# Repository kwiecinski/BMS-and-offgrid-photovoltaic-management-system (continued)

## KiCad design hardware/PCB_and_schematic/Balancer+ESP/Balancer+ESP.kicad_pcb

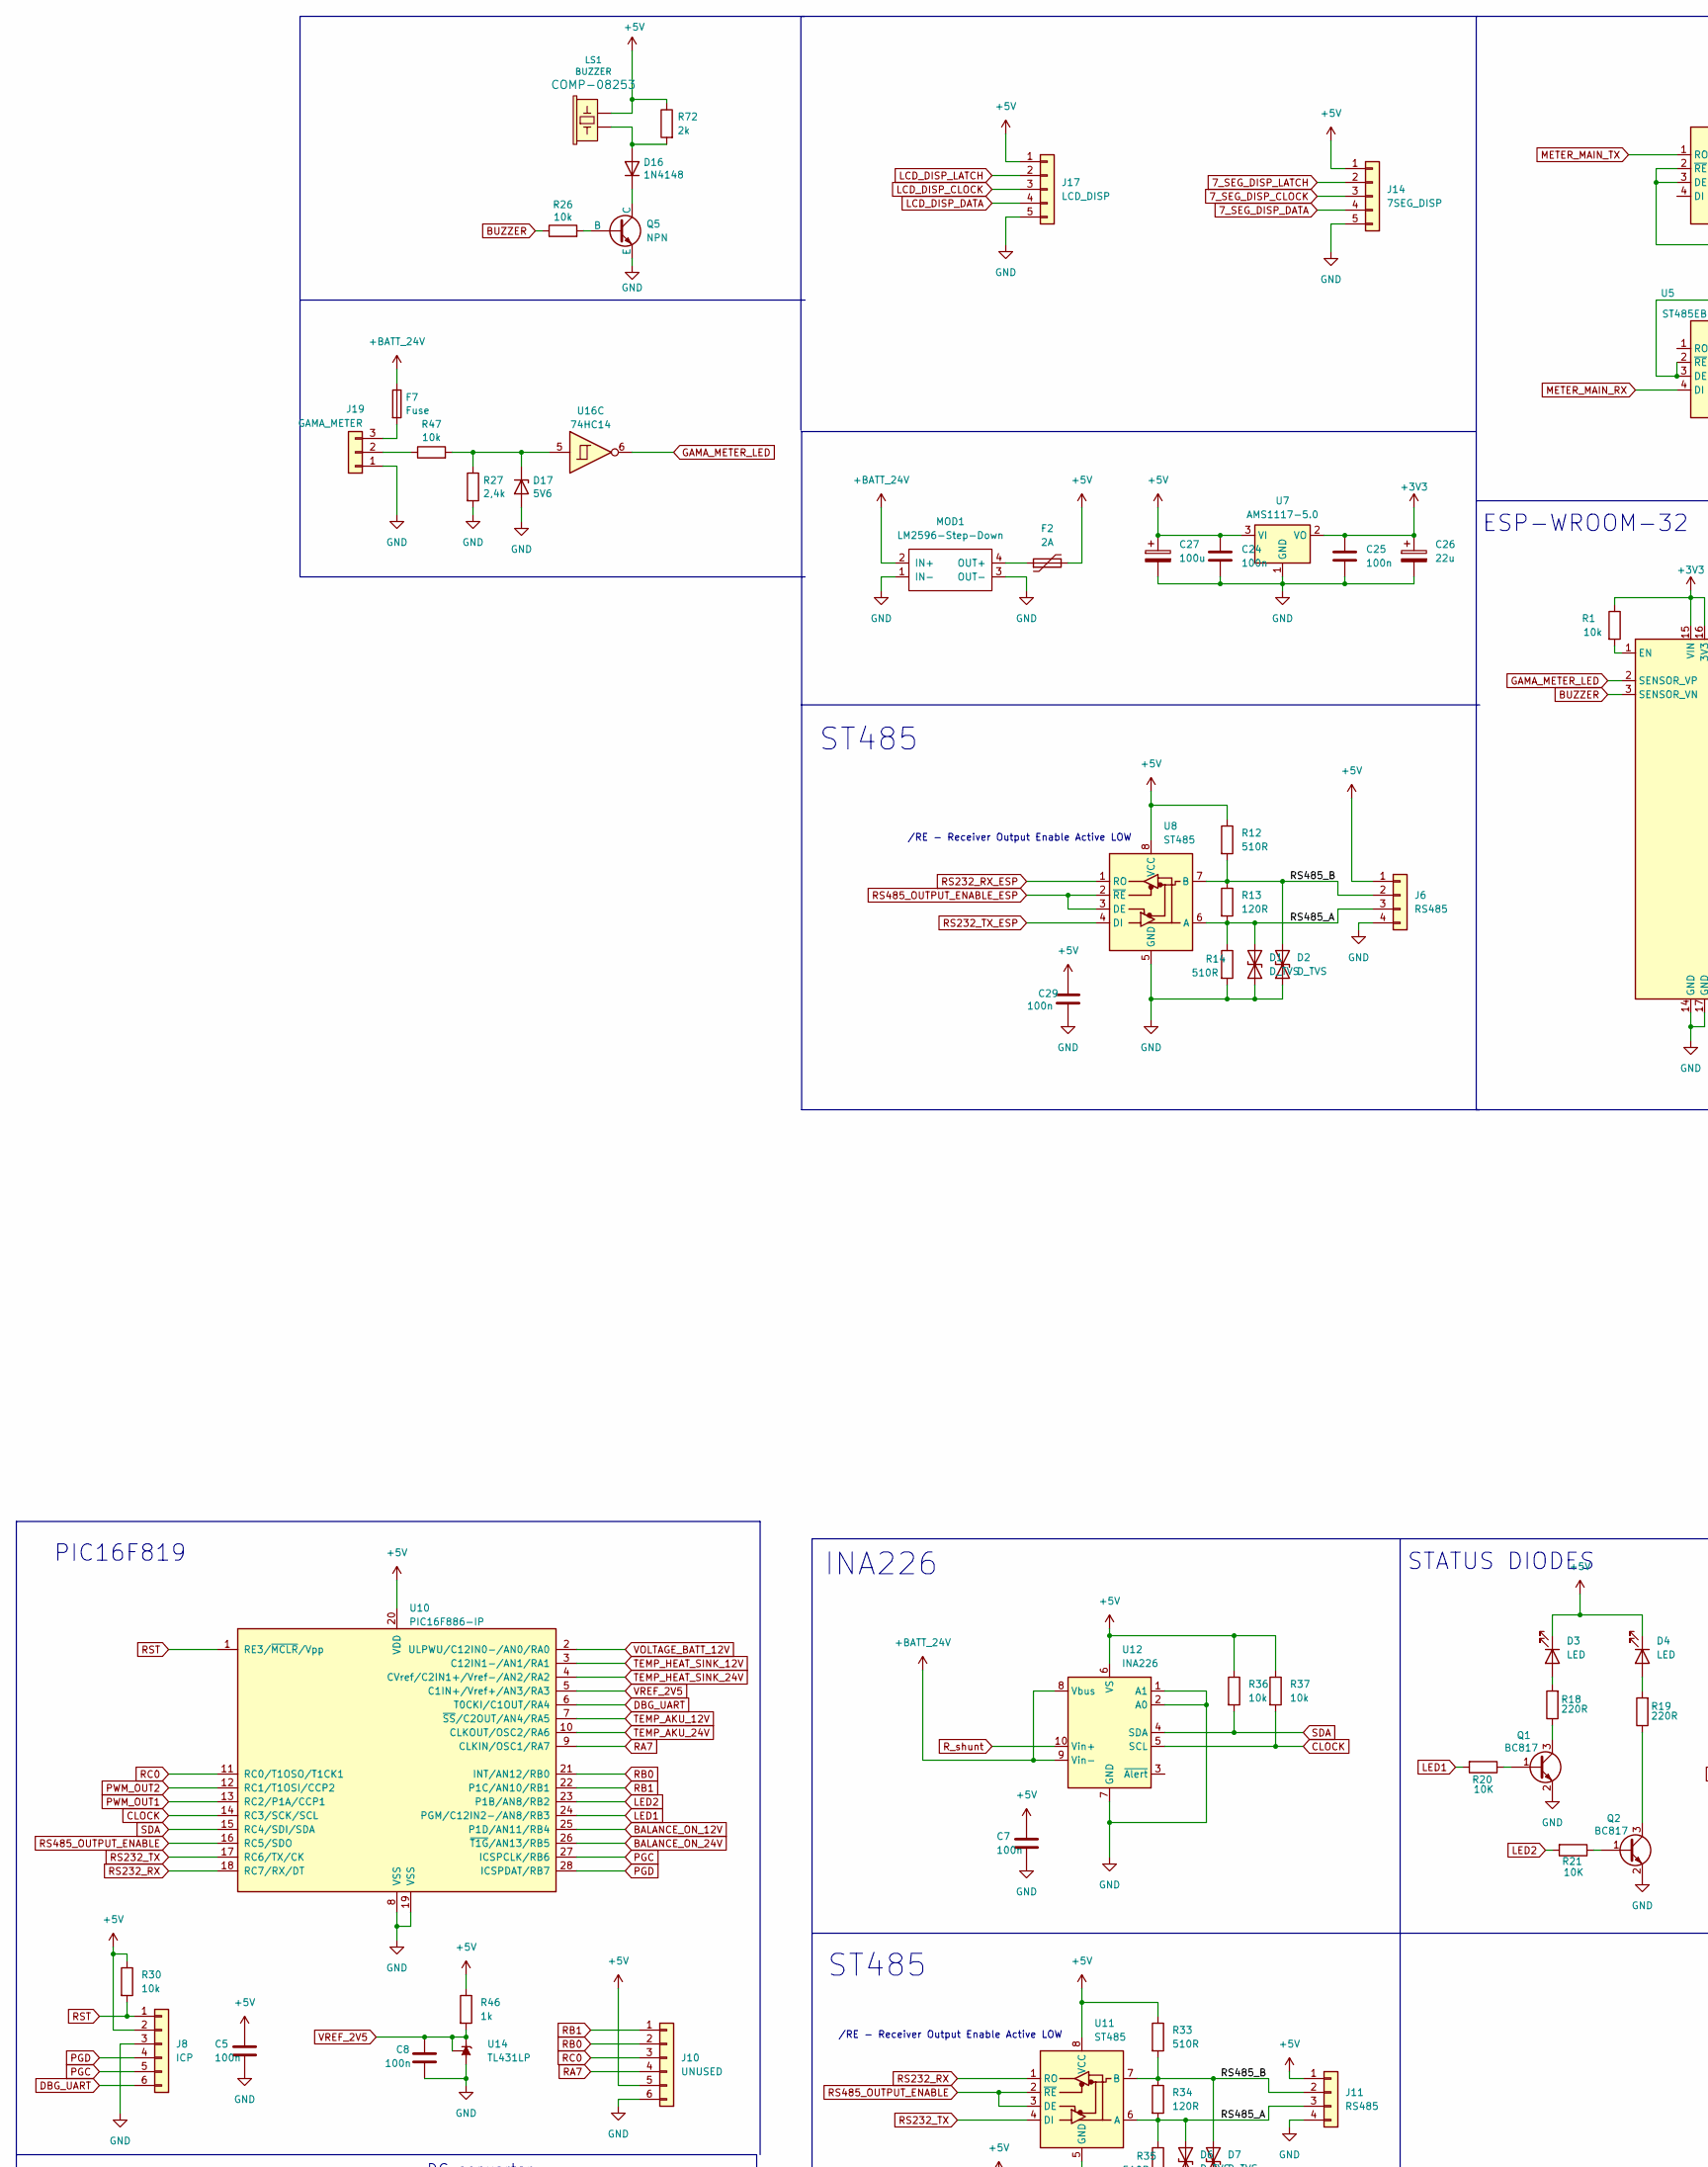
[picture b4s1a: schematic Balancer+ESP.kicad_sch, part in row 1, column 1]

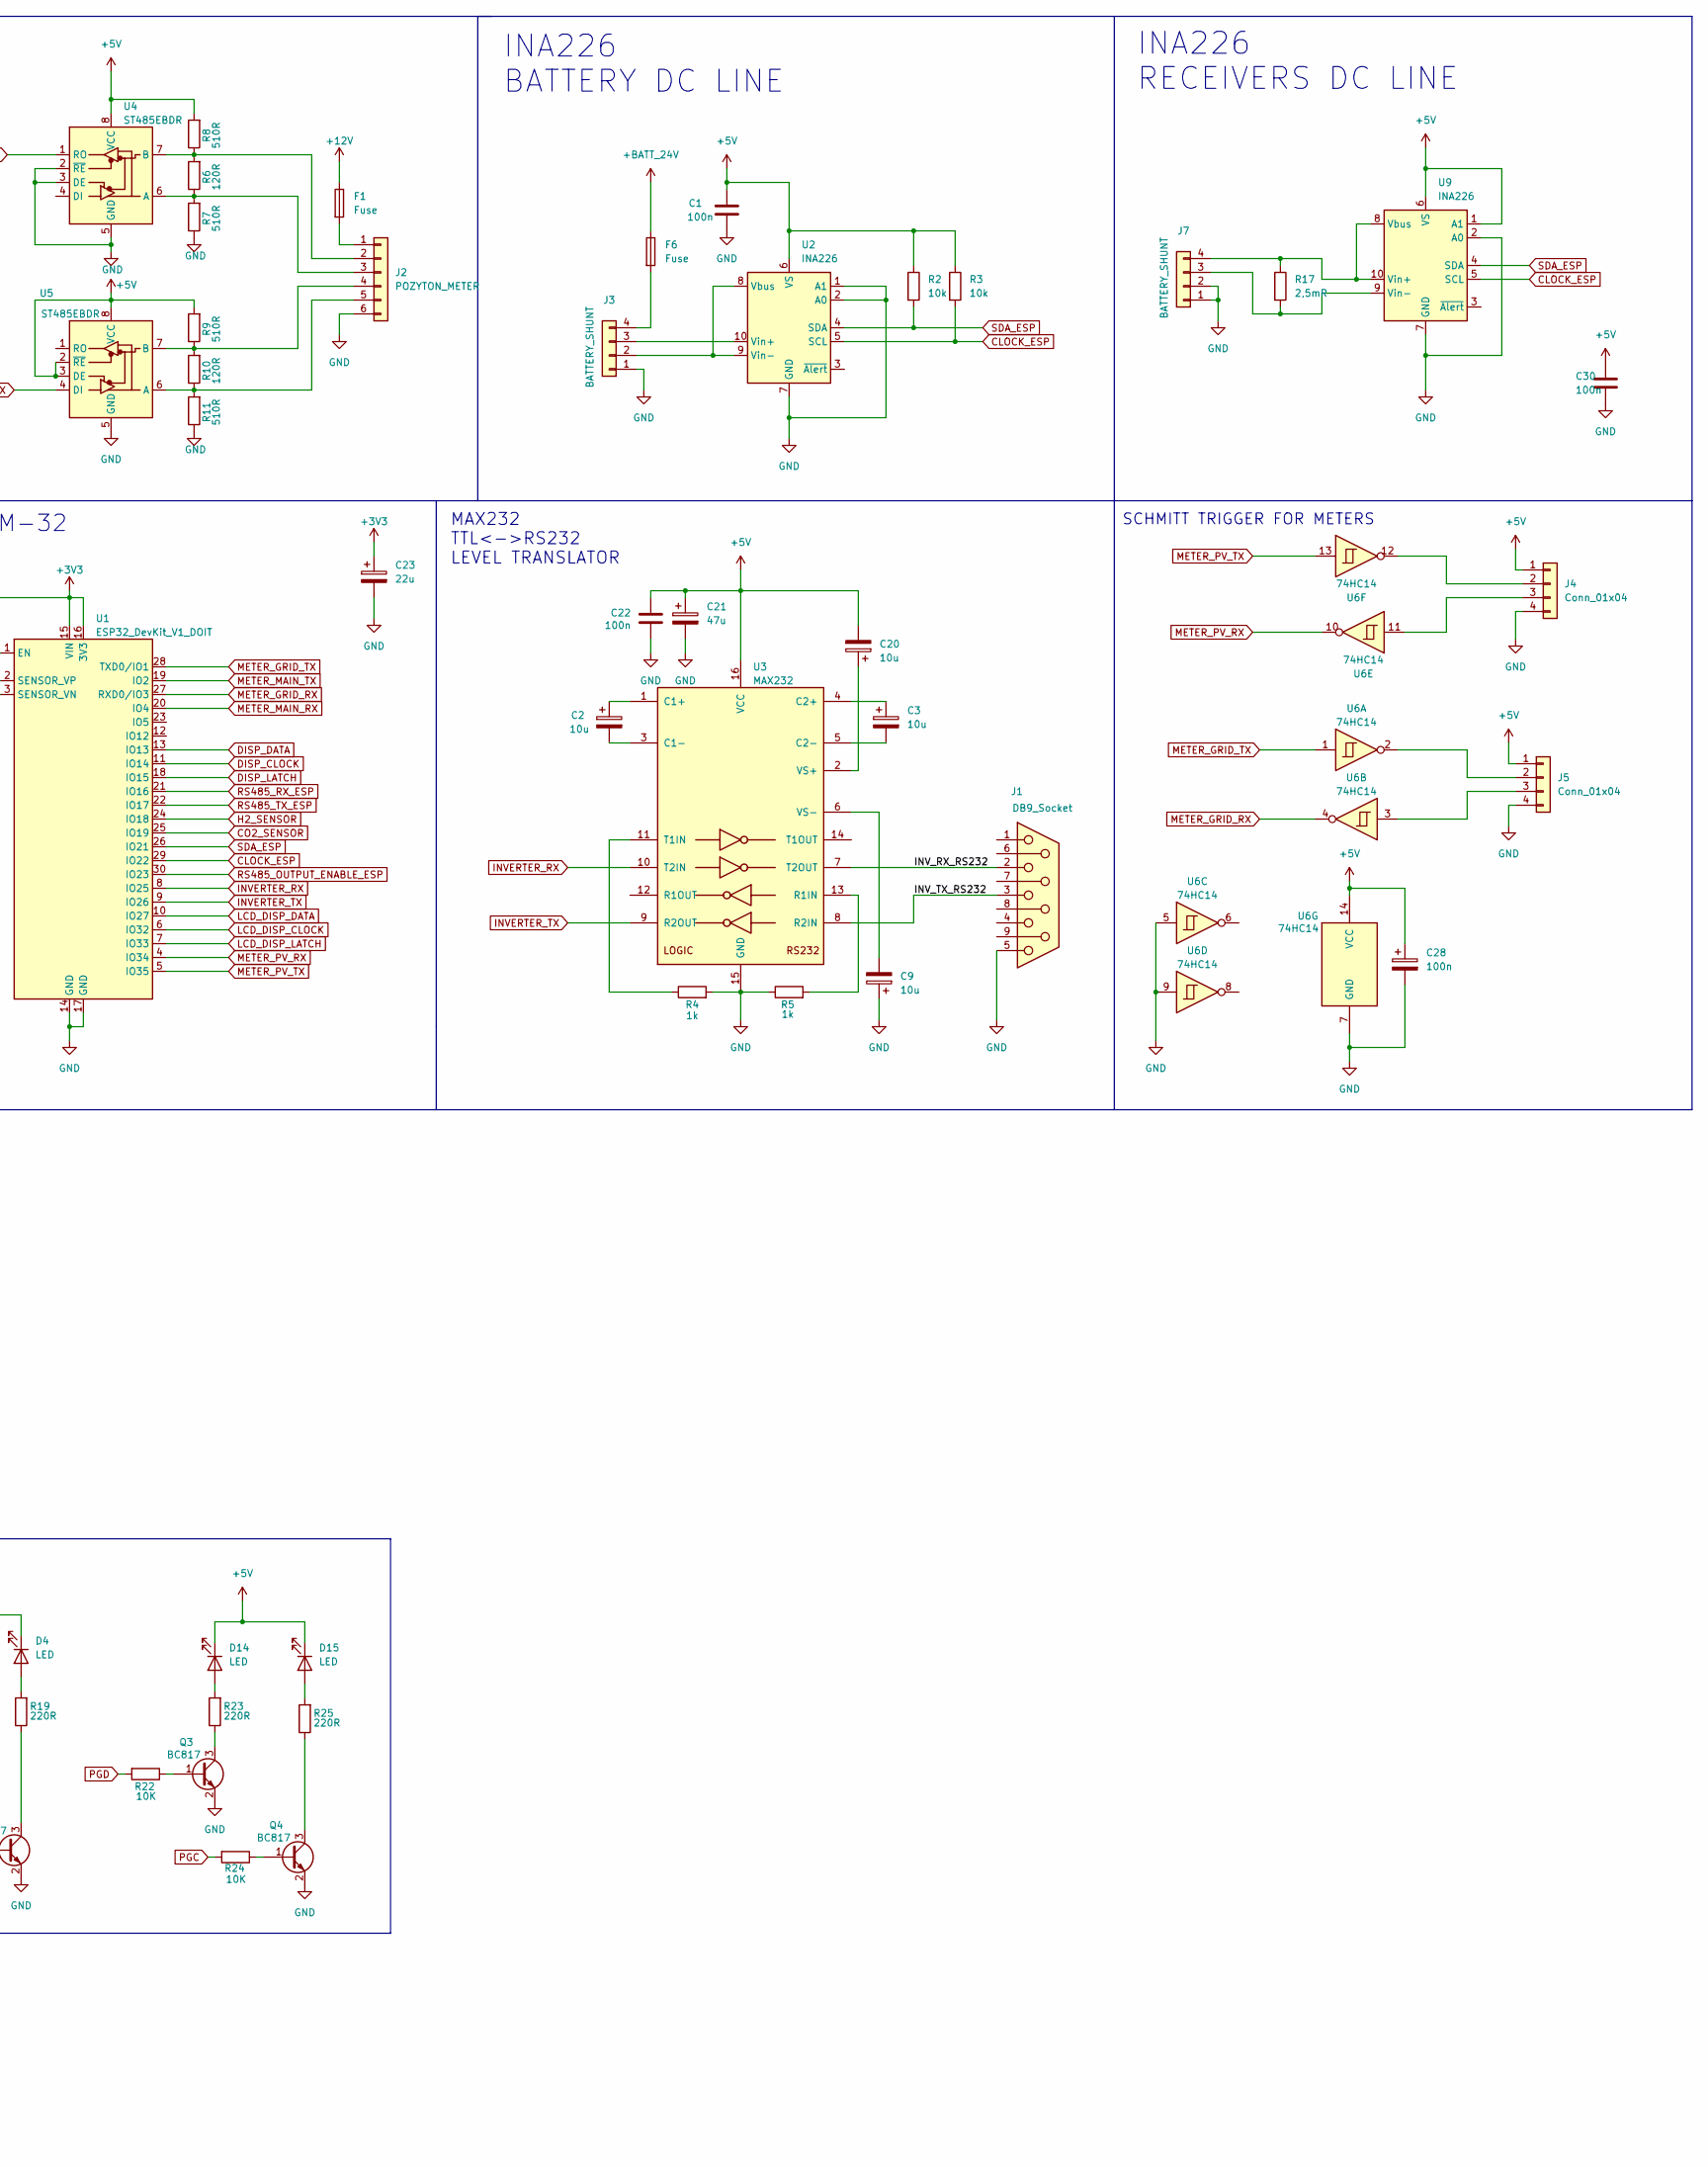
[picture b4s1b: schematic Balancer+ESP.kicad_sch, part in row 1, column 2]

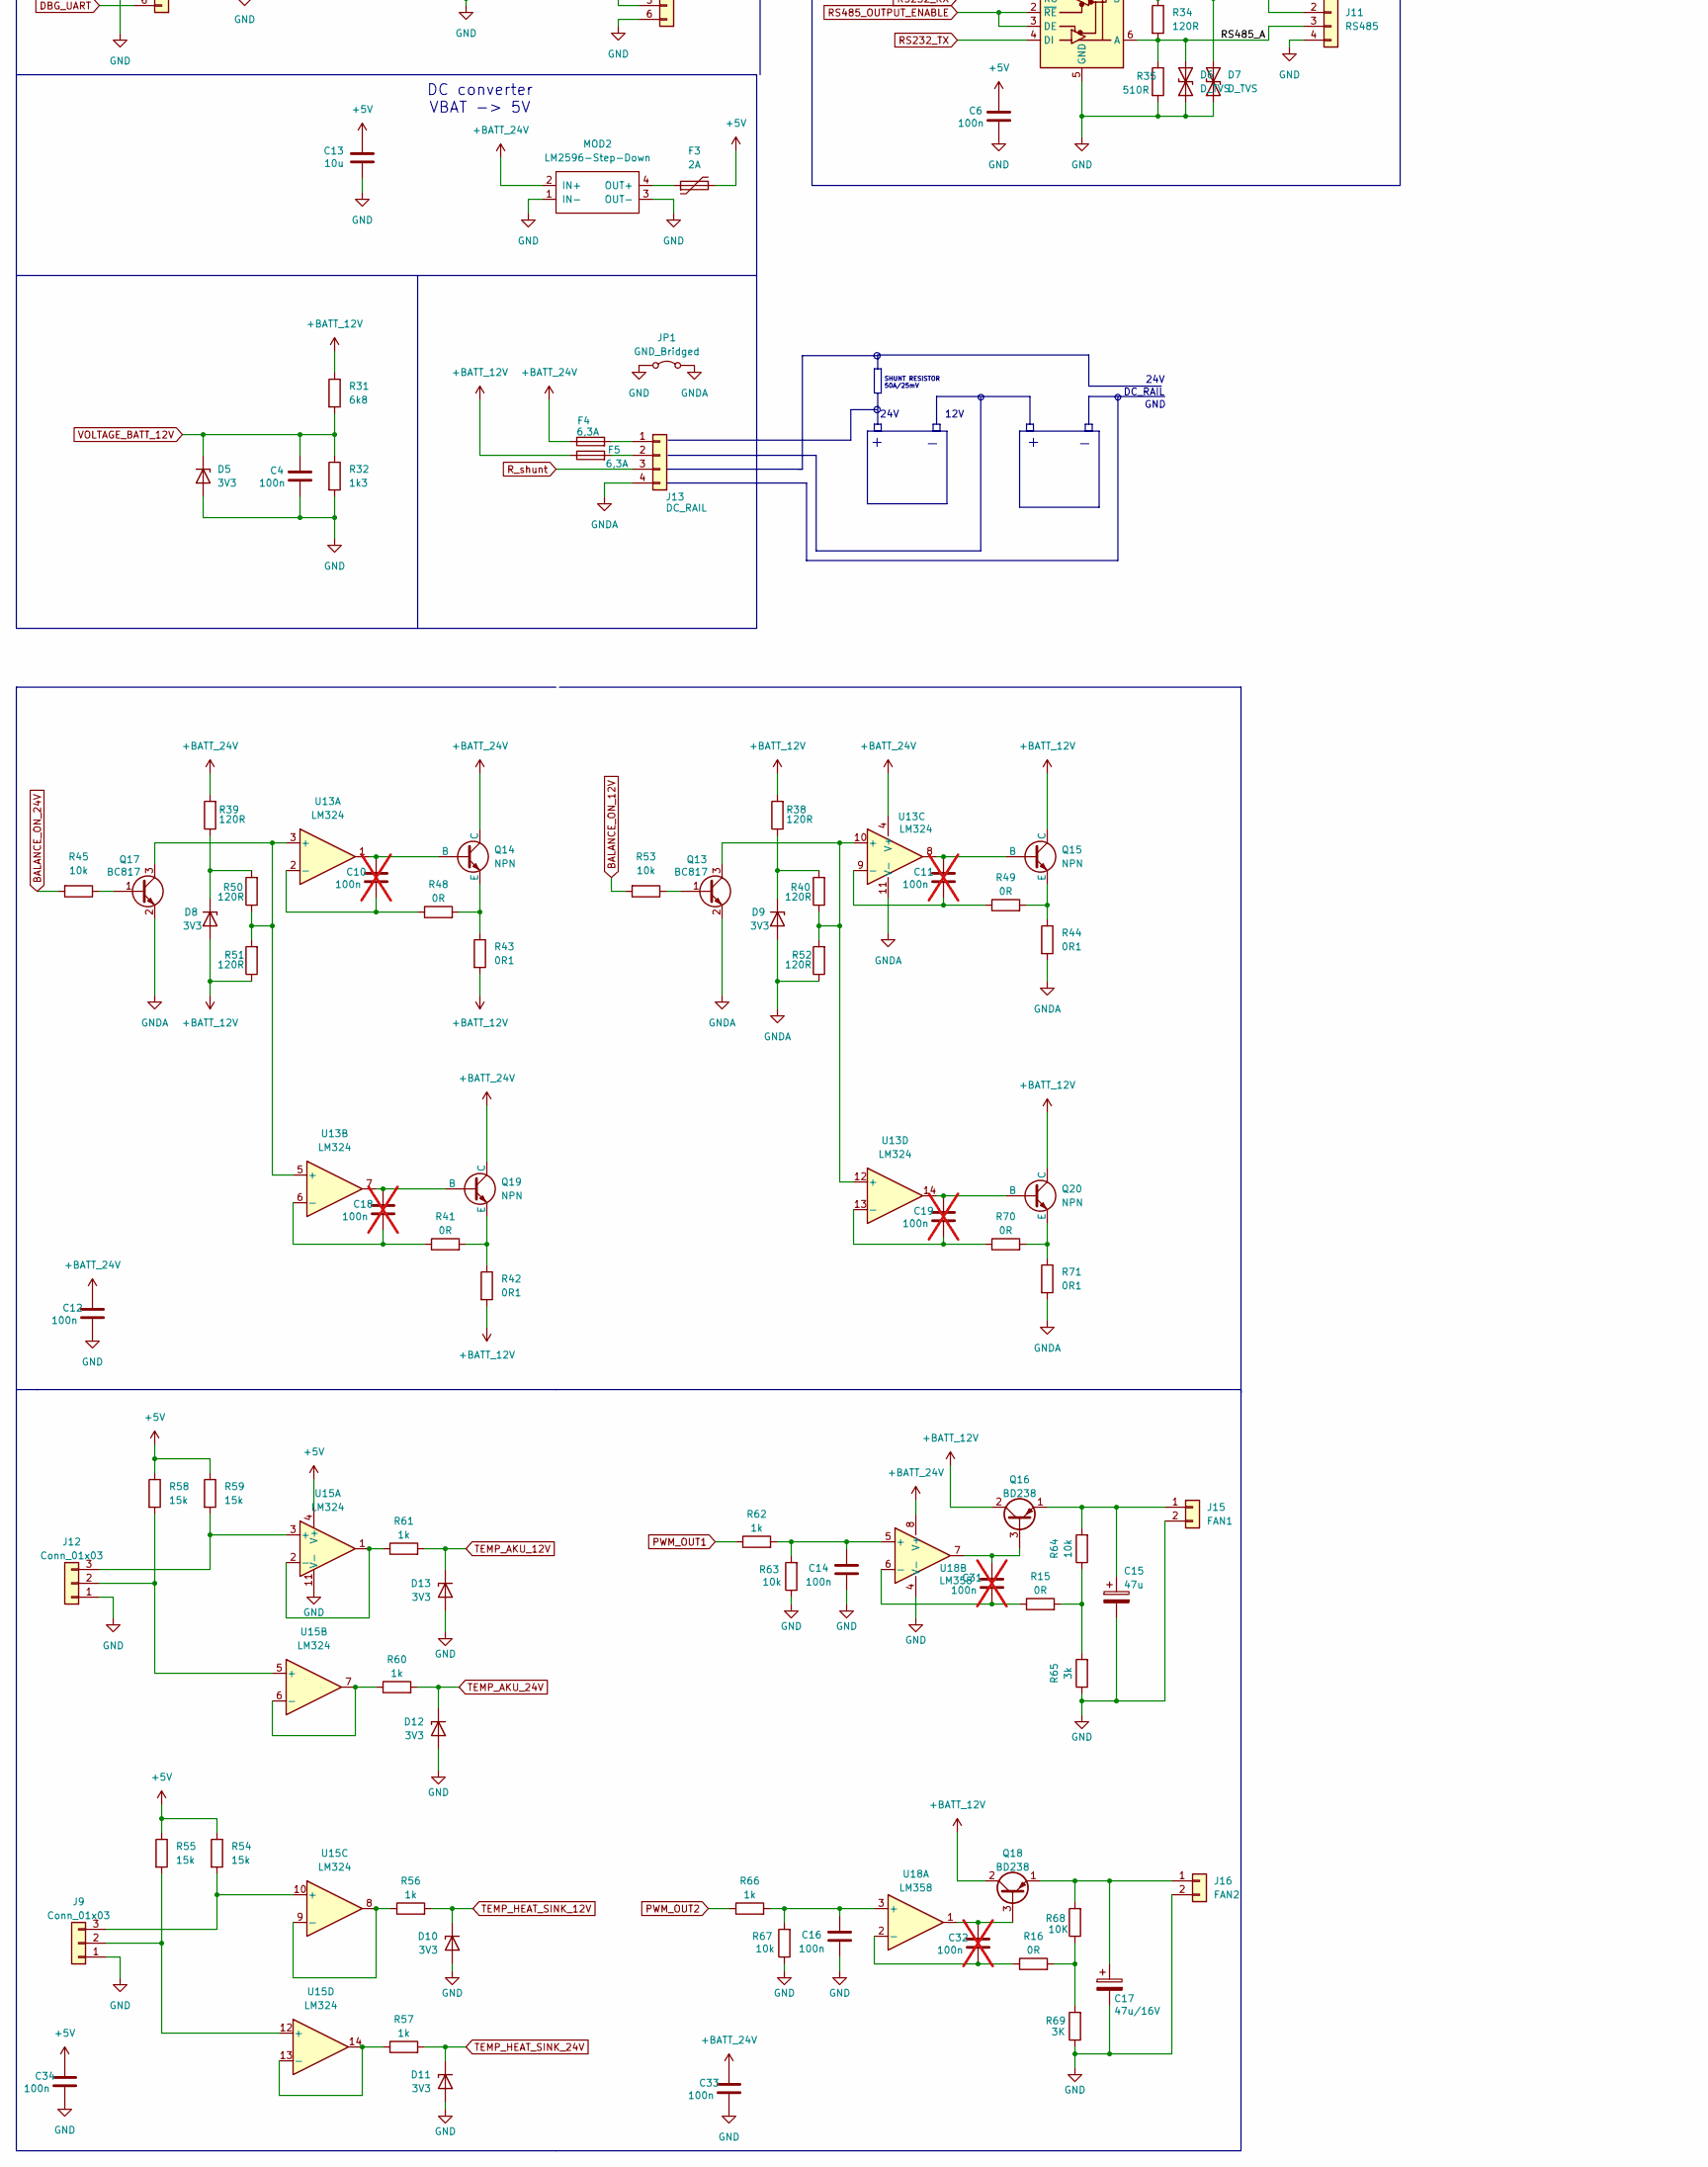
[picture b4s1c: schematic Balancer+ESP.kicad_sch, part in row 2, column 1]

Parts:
C1, C7, C30: 100n; R_0805_2012Metric_Pad1.20x1.40mm_HandSolder
C2, C3, C9, C20: 10u; CP_Radial_D5.0mm_P2.00mm
C4, C5, C6, C8, C12, C14, C16, C24, C25, C29, C33, C34: 100n; C_0805_2012Metric_Pad1.18x1.45mm_HandSolder
C10, C11, C18, C19, C31, C32: 100n; C_0805_2012Metric_Pad1.18x1.45mm_HandSolder; not fitted
C13: 10u; CP_Elec_6.3x4.5
C15, C21: 47u; CP_Radial_D5.0mm_P2.00mm
C17: 47u/16V; CP_Radial_D5.0mm_P2.00mm
C22: 100n; CP_Elec_6.3x4.5
C23: 22u; CP_Radial_D5.0mm_P2.00mm
C26: 22u; CP_Radial_D4.0mm_P1.50mm
C27: 100u; CP_Radial_D4.0mm_P1.50mm
C28: 100n; C_0805_2012Metric
D1, D2, D6, D7: D_TVS; D_SMC
D3, D4, D14, D15: LED; LED_D5.0mm
D5, D8, D9, D10, D11, D12, D13: 3V3; D_MiniMELF
D16: 1N4148; D_MiniMELF
D17: 5V6
F1: Fuse; Fuseholder_Clip-5x20mm_Littelfuse_519_Inline_P20.60x5.00mm_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
F2, F3: 2A; Fuse_2512_6332Metric_Pad1.52x3.35mm_HandSolder
F4, F5: 6,3A; Fuse_2512_6332Metric_Pad1.52x3.35mm_HandSolder
F6: Fuse; Fuseholder_Clip-5x20mm_Littelfuse_520_Inline_P20.50x5.80mm_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
F7: Fuse
J1: DB9_Socket; DSUB-9_Female_Horizontal_P2.77x2.84mm_EdgePinOffset7.70mm_H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
J2: POZYTON_METER; JST_EH_B6B-EH-A_1x06_P2.50mm_Vertical
J3, J7: BATTERY_SHUNT; JST_EH_B4B-EH-A_1x04_P2.50mm_Vertical
J4, J5: Conn_01x04; JST_EH_B4B-EH-A_1x04_P2.50mm_Vertical
J6, J11: RS485; PinHeader_1x04_P2.54mm_Vertical
J8: ICP; PinHeader_1x06_P2.54mm_Vertical
J9, J12: Conn_01x03; JST_EH_B3B-EH-A_1x03_P2.50mm_Vertical
J10: UNUSED; PinHeader_1x06_P2.54mm_Vertical
J13: DC_RAIL; JST_EH_B4B-EH-A_1x04_P2.50mm_Vertical
J14: 7SEG_DISP; JST_EH_B5B-EH-A_1x05_P2.50mm_Vertical
J15: FAN1; JST_EH_B2B-EH-A_1x02_P2.50mm_Vertical
J16: FAN2; JST_EH_B2B-EH-A_1x02_P2.50mm_Vertical
J17: LCD_DISP; JST_EH_B5B-EH-A_1x05_P2.50mm_Vertical
J19: GAMA_METER
JP1: GND_Bridged; SolderJumper-2_P1.3mm_Bridged2Bar_Pad1.0x1.5mm
LS1: BUZZER; Buzzer
MOD1, MOD2: LM2596-Step-Down; MP1504_Mini_3A_Step_Down_Conv
Q1, Q2, Q3, Q4, Q13, Q17: BC817; SOT-23
Q5: NPN
Q14, Q15, Q19, Q20: NPN; TO-220-3_Vertical
Q16, Q18: BD238; TO-126-3_Vertical
R1, R2, R3, R26, R30, R36, R37, R45, R47, R53, R63, R64, R67: 10k; R_0805_2012Metric_Pad1.20x1.40mm_HandSolder
R4, R5, R46, R56, R57, R60, R61, R62, R66: 1k; R_0805_2012Metric_Pad1.20x1.40mm_HandSolder
R6, R10, R13, R34, R38, R39, R40, R50, R51, R52: 120R; R_0805_2012Metric_Pad1.20x1.40mm_HandSolder
R7, R8, R9, R11, R12, R14, R33, R35: 510R; R_0805_2012Metric_Pad1.20x1.40mm_HandSolder
R15, R16, R41, R48, R49, R70: 0R; R_0805_2012Metric_Pad1.20x1.40mm_HandSolder
R17: 2,5mR; R_0805_2012Metric_Pad1.20x1.40mm_HandSolder
R18, R19, R23, R25: 220R; R_0805_2012Metric_Pad1.20x1.40mm_HandSolder
R20, R21, R22, R24, R68: 10K; R_0805_2012Metric_Pad1.20x1.40mm_HandSolder
R27: 2,4k; R_0805_2012Metric_Pad1.20x1.40mm_HandSolder
R31: 6k8; R_0805_2012Metric_Pad1.20x1.40mm_HandSolder
R32: 1k3; R_0805_2012Metric_Pad1.20x1.40mm_HandSolder
R42, R43, R44, R71: 0R1; R_0805_2012Metric_Pad1.20x1.40mm_HandSolder
R54, R55, R58, R59: 15k; R_0805_2012Metric_Pad1.20x1.40mm_HandSolder
R65: 3k; R_0805_2012Metric_Pad1.20x1.40mm_HandSolder
R69: 3K; R_0805_2012Metric_Pad1.20x1.40mm_HandSolder
R72: 2k; 0805
U1: ESP32_DevKit_V1_DOIT; esp32_devkit_v1_doit
U2, U9, U12: INA226; VSSOP-10_3x3mm_P0.5mm
U3: MAX232; SOIC-16W_5.3x10.2mm_P1.27mm
U4, U5: ST485EBDR; SOIC-8_3.9x4.9mm_P1.27mm
U6, U16: 74HC14; SOIC-14_3.9x8.7mm_P1.27mm
U7: AMS1117-5.0; SOT-223-3_TabPin2
U8, U11: ST485; SOIC-8_3.9x4.9mm_P1.27mm
U10: PIC16F886-IP; SOIC-28W_7.5x17.9mm_P1.27mm
U13, U15: LM324; SOIC-14_3.9x8.7mm_P1.27mm
U14: TL431LP; TO-92_Inline
U18: LM358; SO-8_3.9x4.9mm_P1.27mm

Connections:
7_SEG_DISP_CLOCK: J14.3
7_SEG_DISP_DATA: J14.4
7_SEG_DISP_LATCH: J14.2
+3V3: C23.1, C25.1, C26.1, R1.1, U1.15 (VIN), U1.16 (3V3), U7.2 (VO)
+5V: C1.1, C5.1, C6.1, C7.1, C13.2, C20.2, C21.1, C22.2, C24.1, C27.1, C28.1, C29.1, C30.1, C34.1, D3.1 (K), D4.1 (K), D14.1 (K), D15.1 (K), F2.2, F3.2, J4.1, J5.1, J6.1, J8.2, J10.5, J11.1, J14.1, J17.1, LS1.- (2), R2.1, R3.1, R8.2, R9.2, R12.1, R30.1, R33.1, R36.1, R37.1, R46.1, R54.1, R55.1, R58.1, R59.1, R72.1, U2.6 (VS), U3.16 (VCC), U4.8 (VCC), U5.2 (~RE), U5.3 (DE), U5.8 (VCC), U6.14 (VCC), U7.3 (VI), U8.8 (VCC), U9.1 (A1), U9.6 (VS), U10.20 (VDD), U11.8 (VCC), U12.6 (VS), U15.4 (V+)
+12V: F1.1
+BATT_12V: D8.2 (A), F5.1, Q15.1 (C), Q16.2 (C), Q18.2 (C), Q20.1 (C), R31.1, R38.2, R42.2, R43.2, R51.1
+BATT_24V: C12.1, C33.1, F4.1, F6.1, F7.1, MOD1.2 (IN+), MOD2.2 (IN+), Q14.1 (C), Q19.1 (C), R39.2, U12.8 (Vbus), U12.9 (Vin-), U13.4 (V+), U18.8 (V+)
/ESP32_Measurment_Board/INV_RX_RS232: J1.2, U3.7 (T2OUT)
/ESP32_Measurment_Board/INV_TX_RS232: J1.3, U3.8 (R2IN)
BALANCE_ON_12V: R53.2, U10.25 (P1D/AN11/RB4)
BALANCE_ON_24V: R45.2, U10.26 (~T1G/AN13/RB5)
BUZZER: R26.1, U1.3 (SENSOR_VN)
CLOCK: R37.2, U10.14 (RC3/SCK/SCL), U12.5 (SCL)
CLOCK_ESP: R3.2, U1.29 (IO22), U2.5 (SCL), U9.5 (SCL)
CO2_SENSOR: U1.25 (IO19)
DBG_UART: J8.6, U10.6 (T0CKI/C1OUT/RA4)
DISP_CLOCK: U1.11 (IO14)
DISP_DATA: U1.13 (IO13)
DISP_LATCH: U1.18 (IO15)
GAMA_METER_LED: U1.2 (SENSOR_VP), U16.6
GND: C1.2, C4.2, C5.2, C6.2, C7.2, C8.2, C9.1, C12.2, C13.1, C14.2, C15.2, C16.2, C17.2, C21.2, C22.1, C23.2, C24.2, C25.2, C26.2, C27.2, C28.2, C29.2, C30.2, C33.2, C34.2, D1.1 (A1), D2.1 (A1), D5.2 (A), D6.1 (A1), D7.1 (A1), D10.2 (A), D11.2 (A), D12.2 (A), D13.2 (A), D17.2 (A), J1.5, J2.6, J3.1, J4.4, J5.4, J6.4, J7.1, J7.2, J8.3, J9.1, J10.6, J11.4, J12.1, J14.5, J15.2, J16.2, J17.5, J19.1, JP1.1 (A), MOD1.1 (IN-), MOD1.3 (OUT-), MOD2.1 (IN-), MOD2.3 (OUT-), Q1.2 (E), Q2.2 (E), Q3.2 (E), Q4.2 (E), Q5.3 (E), R4.2, R5.1, R7.1, R11.1, R14.2, R27.2, R32.2, R35.2, R63.1, R65.1, R67.1, R69.1, U1.14 (GND), U1.17 (GND), U2.1 (A1), U2.2 (A0), U2.7 (GND), U3.15 (GND), U4.2 (~RE), U4.3 (DE), U4.5 (GND), U5.5 (GND), U6.5, U6.7 (GND), U6.9, U7.1 (GND), U8.5 (GND), U9.2 (A0), U9.7 (GND), U10.8 (VSS), U10.19 (VSS), U11.5 (GND), U12.1 (A1), U12.2 (A0), U12.7 (GND), U14.2 (A), U15.11 (V-), U18.4 (V-)
GNDA: D9.2 (A), J13.4, JP1.2 (B), Q13.2 (E), Q17.2 (E), R44.2, R52.1, R71.2, U13.11 (V-)
H2_SENSOR: U1.24 (IO18)
INVERTER_RX: U1.8 (IO25), U3.10 (T2IN)
INVERTER_TX: U1.9 (IO26), U3.9 (R2OUT)
LCD_DISP_CLOCK: J17.3, U1.6 (IO32)
LCD_DISP_DATA: J17.4, U1.10 (IO27)
LCD_DISP_LATCH: J17.2, U1.7 (IO33)
LED1: R20.2, U10.24 (PGM/C12IN2-/AN8/RB3)
LED2: R21.2, U10.23 (P1B/AN8/RB2)
METER_GRID_RX: U1.27 (RXD0/IO3), U6.4
METER_GRID_TX: U1.28 (TXD0/IO1), U6.1
METER_MAIN_RX: U1.20 (IO4), U5.4 (DI)
METER_MAIN_TX: U1.19 (IO2), U4.1 (RO)
METER_PV_RX: U1.4 (IO34), U6.10
METER_PV_TX: U1.5 (IO35), U6.13
unnamed: D3.2 (A), R18.2
unnamed: D4.2 (A), R19.2
unnamed: D8.1 (K), R39.1, R50.2
unnamed: D9.1 (K), R38.1, R40.2
unnamed: D14.2 (A), R23.2
unnamed: D15.2 (A), R25.2
unnamed: D16.1 (K), Q5.1 (C)
unnamed: D16.2 (A), LS1.+ (1), R72.2
unnamed: D17.1 (K), R27.1, R47.2, U16.5
unnamed: F7.2, J19.3
unnamed: F1.2, J2.1
unnamed: J2.2, R6.2, R8.1, U4.7 (B)
unnamed: J2.3, R6.1, R7.2, U4.6 (A)
unnamed: J2.4, R9.1, R10.2, U5.7 (B)
unnamed: J2.5, R10.1, R11.2, U5.6 (A)
unnamed: J3.2, U2.8 (Vbus), U2.9 (Vin-)
unnamed: J3.3, U2.10 (Vin+)
unnamed: F6.2, J3.4
unnamed: J4.2, U6.12
unnamed: J4.3, U6.11
unnamed: J5.2, U6.2
unnamed: J5.3, U6.3
unnamed: J7.3, R17.2, U9.9 (Vin-)
unnamed: J7.4, R17.1, U9.8 (Vbus), U9.10 (Vin+)
unnamed: J9.2, R55.2, U15.12 (+)
unnamed: J9.3, R54.2, U15.10 (+)
unnamed: J12.2, R58.2, U15.5 (+)
unnamed: J12.3, R59.2, U15.3 (+)
unnamed: F4.2, J13.1
unnamed: F5.2, J13.2
unnamed: C15.1, J15.1, Q16.1 (E), R64.2
unnamed: C17.1, J16.1, Q18.1 (E), R68.2
unnamed: J19.2, R47.1
unnamed: F2.1, MOD1.4 (OUT+)
unnamed: F3.1, MOD2.4 (OUT+)
unnamed: Q1.1 (B), R20.1
unnamed: Q1.3 (C), R18.1
unnamed: Q2.1 (B), R21.1
unnamed: Q2.3 (C), R19.1
unnamed: Q3.1 (B), R22.1
unnamed: Q3.3 (C), R23.1
unnamed: Q4.1 (B), R24.1
unnamed: Q4.3 (C), R25.1
unnamed: Q5.2 (B), R26.2
unnamed: Q13.1 (B), R53.1
unnamed: Q13.3 (C), R40.1, R52.2, U13.10 (+), U13.12 (+)
unnamed: C10.1, Q14.2 (B), U13.1
unnamed: Q14.3 (E), R43.1, R48.2
unnamed: C11.1, Q15.2 (B), U13.8
unnamed: Q15.3 (E), R44.1, R49.2
unnamed: C31.1, Q16.3 (B), U18.7
unnamed: Q17.1 (B), R45.1
unnamed: Q17.3 (C), R50.1, R51.2, U13.3 (+), U13.5 (+)
unnamed: C32.1, Q18.3 (B), U18.1
unnamed: C18.1, Q19.2 (B), U13.7
unnamed: Q19.3 (E), R41.2, R42.1
unnamed: C19.1, Q20.2 (B), U13.14
unnamed: Q20.3 (E), R70.2, R71.1
unnamed: R15.2, R64.1, R65.2
unnamed: R16.2, R68.1, R69.2
unnamed: R1.2, U1.1 (EN)
unnamed: C2.1, U3.1 (C1+)
unnamed: C2.2, U3.3 (C1-)
unnamed: C3.1, U3.4 (C2+)
unnamed: C3.2, U3.5 (C2-)
unnamed: R5.2, U3.13 (R1IN)
unnamed: R4.1, U3.11 (T1IN)
unnamed: C20.1, U3.2 (VS+)
unnamed: C9.2, U3.6 (VS-)
unnamed: C10.2, R48.1, U13.2 (-)
unnamed: C18.2, R41.1, U13.6 (-)
unnamed: C11.2, R49.1, U13.9 (-)
unnamed: C19.2, R70.1, U13.13 (-)
unnamed: R61.1, U15.1, U15.2 (-)
unnamed: R60.1, U15.6 (-), U15.7
unnamed: R56.1, U15.8, U15.9 (-)
unnamed: R57.1, U15.13 (-), U15.14
unnamed: C16.1, R66.2, R67.2, U18.3 (+)
unnamed: C32.2, R16.1, U18.2 (-)
unnamed: C14.1, R62.2, R63.2, U18.5 (+)
unnamed: C31.2, R15.1, U18.6 (-)
PGC: J8.5, R24.2, U10.27 (ICSPCLK/RB6)
PGD: J8.4, R22.2, U10.28 (ICSPDAT/RB7)
PWM_OUT1: R62.1, U10.13 (RC2/P1A/CCP1)
PWM_OUT2: R66.1, U10.12 (RC1/T1OSI/CCP2)
RA7: J10.4, U10.9 (CLKIN/OSC1/RA7)
RB0: J10.2, U10.21 (INT/AN12/RB0)
RB1: J10.1, U10.22 (P1C/AN10/RB1)
RC0: J10.3, U10.11 (RC0/T1OSO/T1CK1)
RS232_RX: U10.18 (RC7/RX/DT), U11.1 (RO)
RS232_RX_ESP: U8.1 (RO)
RS232_TX: U10.17 (RC6/TX/CK), U11.4 (DI)
RS232_TX_ESP: U8.4 (DI)
RS485_OUTPUT_ENABLE: U10.16 (RC5/SDO), U11.2 (~RE), U11.3 (DE)
RS485_OUTPUT_ENABLE_ESP: U1.30 (IO23), U8.2 (~RE), U8.3 (DE)
RS485_RX_ESP: U1.21 (IO16)
RS485_TX_ESP: U1.22 (IO17)
RST: J8.1, R30.2, U10.1 (RE3/~MCLR/Vpp)
R_shunt: J13.3, U12.10 (Vin+)
SDA: R36.2, U10.15 (RC4/SDI/SDA), U12.4 (SDA)
SDA_ESP: R2.2, U1.26 (IO21), U2.4 (SDA), U9.4 (SDA)
TEMP_AKU_12V: D13.1 (K), R61.2, U10.7 (~SS/C2OUT/AN4/RA5)
TEMP_AKU_24V: D12.1 (K), R60.2, U10.10 (CLKOUT/OSC2/RA6)
TEMP_HEAT_SINK_12V: D10.1 (K), R56.2, U10.3 (C12IN1-/AN1/RA1)
TEMP_HEAT_SINK_24V: D11.1 (K), R57.2, U10.4 (CVref/C2IN1+/Vref-/AN2/RA2)
VOLTAGE_BATT_12V: C4.1, D5.1 (K), R31.2, R32.1, U10.2 (ULPWU/C12IN0-/AN0/RA0)
VREF_2V5: C8.1, R46.2, U10.5 (C1IN+/Vref+/AN3/RA3), U14.1 (REF), U14.3 (K)

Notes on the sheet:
/RE - Receiver Output Enable Active LOW
PIC16F819
DC_RAIL
ESP-WROOM-32
SHUNT RESISTOR 50A/25mV
MAX232 TTL<->RS232 LEVEL TRANSLATOR
ST485
GND
INA226 RECEIVERS DC LINE
12V
INA226 BATTERY DC LINE
DC converter VBAT -> 5V
STATUS DIODES
24V
SCHMITT TRIGGER FOR METERS
INA226

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
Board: 2 copper layers, 173 parts (13 on the bottom side), 130 nets, no tracks yet.

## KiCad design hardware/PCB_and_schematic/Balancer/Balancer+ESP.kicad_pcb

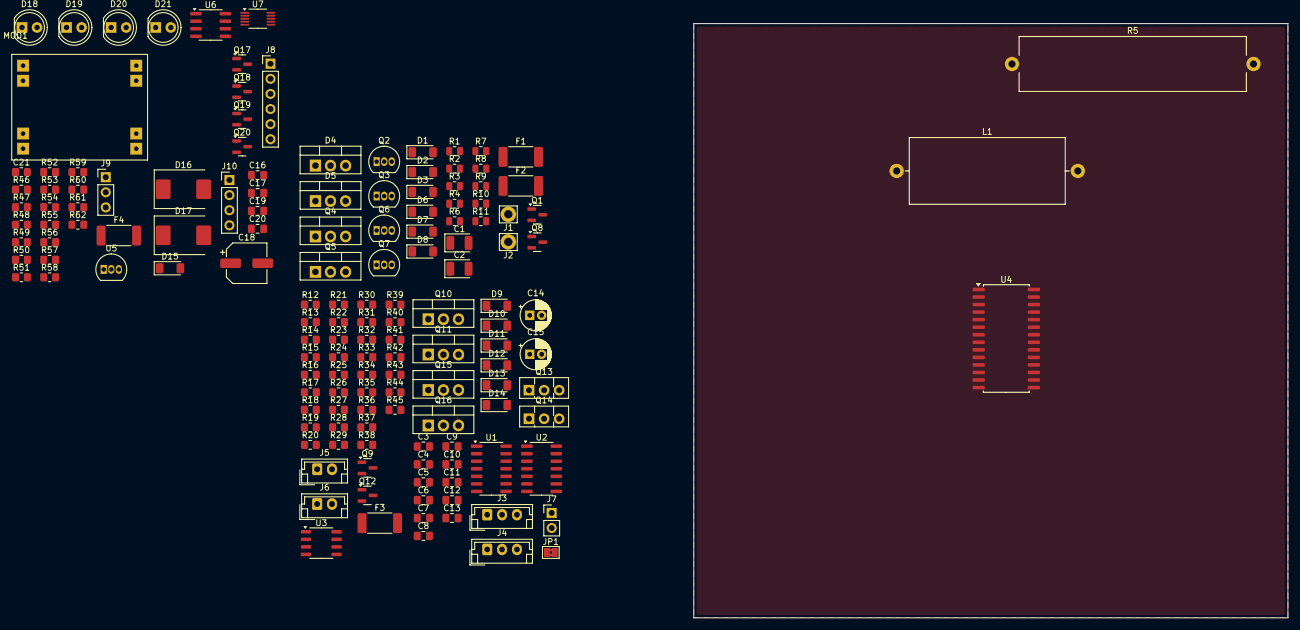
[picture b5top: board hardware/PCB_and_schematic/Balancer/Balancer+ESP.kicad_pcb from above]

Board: 2 copper layers, 100.0 x 100.0 mm, 148 parts (0 on the bottom side), 98 nets, no tracks yet.

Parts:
C1, C2: 22u; CP_EIA-3528-21_Kemet-B
C3, C4, C5, C6, C7, C8, C9, C10, C11, C12, C13, C16, C17, C19, C20: 100n; C_0805_2012Metric_Pad1.18x1.45mm_HandSolder
C14: 47u/16V; CP_Radial_D5.0mm_P2.00mm
C15: 47u; CP_Radial_D5.0mm_P2.00mm
C18: 10u; CP_Elec_6.3x4.5
C21: 100n; R_0805_2012Metric_Pad1.20x1.40mm_HandSolder
D1, D8: LL4148; D_MiniMELF
D2, D7: 11V; D_MiniMELF
D3, D6: 18V; D_MiniMELF
D4, D5: D_Schottk; TO-220-3_Vertical
D9, D10, D11, D12, D13, D14, D15: 3V3; D_MiniMELF
D16, D17: D_TVS; D_SMC
D18, D19, D20, D21: LED; LED_D5.0mm
F1, F3: 6,3A; Fuse_2512_6332Metric_Pad1.52x3.35mm_HandSolder
F2, F4: 2A; Fuse_2512_6332Metric_Pad1.52x3.35mm_HandSolder
J1: BATT; Pin_D1.4mm_L8.5mm_W2.8mm_FlatFork
J2: OUT; Pin_D1.4mm_L8.5mm_W2.8mm_FlatFork
J3, J4: Conn_01x03; JST_EH_B3B-EH-A_1x03_P2.50mm_Vertical
J5: FAN1; JST_EH_B2B-EH-A_1x02_P2.50mm_Vertical
J6: FAN2; JST_EH_B2B-EH-A_1x02_P2.50mm_Vertical
J7: Batt; PinHeader_1x02_P2.54mm_Vertical
J8: ICP; PinHeader_1x06_P2.54mm_Vertical
J9: Conn_01x03; PinHeader_1x03_P2.54mm_Vertical
J10: RS485; PinHeader_1x04_P2.54mm_Vertical
JP1: GND_Bridged; SolderJumper-2_P1.3mm_Bridged2Bar_Pad1.0x1.5mm
L1: L; L_Axial_L26.0mm_D11.0mm_P30.48mm_Horizontal_Fastron_77A
MOD1: LM2596-Step-Down; MP1504_Mini_3A_Step_Down_Conv
Q1, Q8, Q9, Q12, Q17, Q18, Q19, Q20: BC817; SOT-23
Q2, Q6: BC337; TO-92_Inline
Q3, Q7: BC327; TO-92_Inline
Q4, Q5: PMOS; TO-220-3_Vertical
Q10, Q11, Q15, Q16: NPN; TO-220-3_Vertical
Q13, Q14: BD238; TO-126-3_Vertical
R1, R11: 4k7; R_0805_2012Metric
R2, R3, R8, R10: 10k; R_0805_2012Metric
R4, R9: 1k; R_0805_2012Metric
R5: 20A/75mV; R_Axial_Power_L38.0mm_W9.0mm_P40.64mm
R6, R7: 100R; R_0805_2012Metric
R12, R28, R32, R33, R44, R46, R53, R54: 10k; R_0805_2012Metric_Pad1.20x1.40mm_HandSolder
R13, R14, R16, R17: 15k; R_0805_2012Metric_Pad1.20x1.40mm_HandSolder
R15, R18, R19, R31, R34, R35, R51: 120R; R_0805_2012Metric_Pad1.20x1.40mm_HandSolder
R20, R21, R22, R23, R29, R30, R49: 1k; R_0805_2012Metric_Pad1.20x1.40mm_HandSolder
R24, R25, R36, R37, R38, R39: 0R; R_0805_2012Metric_Pad1.20x1.40mm_HandSolder
R26, R27, R40, R41: 0R1; R_0805_2012Metric_Pad1.20x1.40mm_HandSolder
R42, R55, R57, R59, R61: 10K; R_0805_2012Metric_Pad1.20x1.40mm_HandSolder
R43: 3K; R_0805_2012Metric_Pad1.20x1.40mm_HandSolder
R45: 3k; R_0805_2012Metric_Pad1.20x1.40mm_HandSolder
R47: 6k8; R_0805_2012Metric_Pad1.20x1.40mm_HandSolder
R48: 1k3; R_0805_2012Metric_Pad1.20x1.40mm_HandSolder
R50, R52: 510R; R_0805_2012Metric_Pad1.20x1.40mm_HandSolder
R56, R58, R60, R62: 220R; R_0805_2012Metric_Pad1.20x1.40mm_HandSolder
U1, U2: LM324; SOIC-14_3.9x8.7mm_P1.27mm
U3: LM358; SO-8_3.9x4.9mm_P1.27mm
U4: PIC16F886-IP; SOIC-28W_7.5x17.9mm_P1.27mm
U5: TL431LP; TO-92_Inline
U6: ST485; SOIC-8_3.9x4.9mm_P1.27mm
U7: INA226; VSSOP-10_3x3mm_P0.5mm

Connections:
+5V: C3.1, C16.1, C18.2, C20.1, C21.1, D18.1 (K), D19.1 (K), D20.1 (K), D21.1 (K), F4.2, J8.2, J9.2, J10.1, R13.1, R14.1, R16.1, R17.1, R46.1, R49.1, R50.1, R53.1, R54.1, U1.4 (V+), U4.20 (VDD), U6.8 (VCC), U7.6 (VS)
+BATT_12V: D9.2 (A), F3.1, Q13.2 (C), Q14.2 (C), Q15.1 (C), Q16.1 (C), R19.1, R26.2, R27.2, R31.2, R47.1
+BATT_24V: C4.1, C7.1, F2.1, MOD1.2 (IN+), Q10.1 (C), Q11.1 (C), R15.2, U2.4 (V+), U3.8 (V+), U7.8 (Vbus), U7.9 (Vin-)
/BMS_microcontroller/RS485_A: D16.2 (A2), J10.3, R51.2, R52.1, U6.6 (A)
/BMS_microcontroller/RS485_B: D17.2 (A2), J10.2, R50.2, R51.1, U6.7 (B)
BALANCE_ON_12V: R28.2, U4.25 (P1D/AN11/RB4)
BALANCE_ON_24V: R12.2, U4.26 (~T1G/AN13/RB5)
CLOCK: R54.2, U4.14 (RC3/SCK/SCL), U7.5 (SCL)
DBG_UART: J8.6, U4.6 (T0CKI/C1OUT/RA4)
DC_LINE_24V: C2.1, D6.1 (K), J2.1, Q5.3 (S), Q6.1 (C), R8.2
GND: C3.2, C4.2, C7.2, C8.2, C9.2, C14.2, C15.2, C16.2, C17.2, C18.1, C19.2, C20.2, C21.2, D10.2 (A), D11.2 (A), D12.2 (A), D13.2 (A), D15.2 (A), D16.1 (A1), D17.1 (A1), J3.1, J4.1, J5.2, J6.2, J8.3, J9.3, J10.4, JP1.1 (A), MOD1.1 (IN-), MOD1.3 (OUT-), Q17.2 (E), Q18.2 (E), Q19.2 (E), Q20.2 (E), R32.1, R33.1, R43.1, R45.1, R48.2, R52.2, U1.11 (V-), U3.4 (V-), U4.8 (VSS), U4.19 (VSS), U5.2 (A), U6.5 (GND), U7.1 (A1), U7.2 (A0), U7.7 (GND)
GNDA: C1.2, C2.2, D2.2 (A), D4.1 (A), D5.1 (A), D7.2 (A), D14.2 (A), J7.2, JP1.2 (B), Q1.2 (E), Q8.2 (E), Q9.2 (E), Q12.2 (E), R2.1, R10.1, R35.1, R40.2, R41.2, U2.11 (V-)
LED1: R55.2, U4.24 (PGM/C12IN2-/AN8/RB3)
LED2: R57.2, U4.23 (P1B/AN8/RB2)
unnamed: D1.2 (A), Q1.1 (B), R1.2, R2.2
unnamed: D2.1 (K), Q3.1 (C)
unnamed: D3.2 (A), Q4.2 (G), R6.2
unnamed: D6.2 (A), Q5.2 (G), R7.2
unnamed: D7.1 (K), Q7.1 (C)
unnamed: D8.2 (A), Q8.1 (B), R10.2, R11.2
unnamed: D9.1 (K), R15.1, R18.2
unnamed: D14.1 (K), R31.1, R34.2
unnamed: D18.2 (A), R56.2
unnamed: D19.2 (A), R58.2
unnamed: D20.2 (A), R60.2
unnamed: D21.2 (A), R62.2
unnamed: F1.2, F2.2, R5.1
unnamed: F1.1, J1.1
unnamed: J3.2, R13.2, U1.5 (+)
unnamed: J3.3, R16.2, U1.3 (+)
unnamed: J4.2, R14.2, U1.12 (+)
unnamed: J4.3, R17.2, U1.10 (+)
unnamed: C15.1, J5.1, Q14.1 (E), R44.2
unnamed: C14.1, J6.1, Q13.1 (E), R42.2
unnamed: F3.2, J7.1
unnamed: F4.1, MOD1.4 (OUT+)
unnamed: Q1.3 (C), R4.1
unnamed: Q2.2 (B), Q3.2 (B), R3.1, R4.2
unnamed: Q2.3 (E), Q3.3 (E), R6.1
unnamed: D4.2 (K), D4.3 (K), L1.1, Q4.1 (D)
unnamed: D5.2 (K), D5.3 (K), L1.2, Q5.1 (D)
unnamed: Q6.2 (B), Q7.2 (B), R8.1, R9.2
unnamed: Q6.3 (E), Q7.3 (E), R7.1
unnamed: Q8.3 (C), R9.1
unnamed: Q9.1 (B), R12.1
unnamed: Q9.3 (C), R18.1, R19.2, U2.3 (+), U2.5 (+)
unnamed: C5.1, Q10.2 (B), U2.1
unnamed: Q10.3 (E), R24.2, R26.1
unnamed: C6.1, Q11.2 (B), U2.7
unnamed: Q11.3 (E), R25.2, R27.1
unnamed: Q12.1 (B), R28.1
unnamed: Q12.3 (C), R34.1, R35.2, U2.10 (+), U2.12 (+)
unnamed: C12.1, Q13.3 (B), U3.1
unnamed: C13.1, Q14.3 (B), U3.7
unnamed: C10.1, Q15.2 (B), U2.8
unnamed: Q15.3 (E), R36.2, R40.1
unnamed: C11.1, Q16.2 (B), U2.14
unnamed: Q16.3 (E), R37.2, R41.1
unnamed: Q17.1 (B), R55.1
unnamed: Q17.3 (C), R56.1
unnamed: Q18.1 (B), R57.1
unnamed: Q18.3 (C), R58.1
unnamed: Q19.1 (B), R59.1
unnamed: Q19.3 (C), R60.1
unnamed: Q20.1 (B), R61.1
unnamed: Q20.3 (C), R62.1
unnamed: R38.2, R42.1, R43.2
unnamed: R39.2, R44.1, R45.2
unnamed: R21.1, U1.1, U1.2 (-)
unnamed: R20.1, U1.6 (-), U1.7
unnamed: R23.1, U1.8, U1.9 (-)
unnamed: R22.1, U1.13 (-), U1.14
unnamed: C5.2, R24.1, U2.2 (-)
unnamed: C6.2, R25.1, U2.6 (-)
unnamed: C10.2, R36.1, U2.9 (-)
unnamed: C11.2, R37.1, U2.13 (-)
unnamed: C8.1, R29.2, R32.2, U3.3 (+)
unnamed: C12.2, R38.1, U3.2 (-)
unnamed: C9.1, R30.2, R33.2, U3.5 (+)
unnamed: C13.2, R39.1, U3.6 (-)
PGC: J8.5, R61.2, U4.27 (ICSPCLK/RB6)
PGD: J8.4, R59.2, U4.28 (ICSPDAT/RB7)
PWM_OUT1: R30.1, U4.21 (INT/AN12/RB0)
PWM_OUT2: R29.1, U4.22 (P1C/AN10/RB1)
PWM_OUT_CHRG: D8.1 (K), R11.1, U4.13 (RC2/P1A/CCP1)
PWM_OUT_DISCH: D1.1 (K), R1.1, U4.12 (RC1/T1OSI/CCP2)
RS232_RX: U4.18 (RC7/RX/DT), U6.1 (RO)
RS232_TX: U4.17 (RC6/TX/CK), U6.4 (DI)
RS485_OUTPUT_ENABLE: U4.16 (RC5/SDO), U6.2 (~RE), U6.3 (DE)
RST: J8.1, R46.2, U4.1 (RE3/~MCLR/Vpp)
R_shunt: C1.1, D3.1 (K), Q2.1 (C), Q4.3 (S), R3.2, R5.2, U7.10 (Vin+)
SDA: R53.2, U4.15 (RC4/SDI/SDA), U7.4 (SDA)
TEMP_AKU_12V: D11.1 (K), R21.2, U4.7 (~SS/C2OUT/AN4/RA5)
TEMP_AKU_24V: D10.1 (K), R20.2, U4.10 (CLKOUT/OSC2/RA6)
TEMP_HEAT_SINK_12V: D13.1 (K), R23.2, U4.3 (C12IN1-/AN1/RA1)
TEMP_HEAT_SINK_24V: D12.1 (K), R22.2, U4.4 (CVref/C2IN1+/Vref-/AN2/RA2)
VOLTAGE_BATT_12V: C17.1, D15.1 (K), R47.2, R48.1, U4.2 (ULPWU/C12IN0-/AN0/RA0)
VREF_2V5: C19.1, R49.2, U4.5 (C1IN+/Vref+/AN3/RA3), U5.1 (REF), U5.3 (K)
